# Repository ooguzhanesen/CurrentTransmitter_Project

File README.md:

# CURRENT TRANSMITTER KARTI
## KART ÖZELLİKLERİ
- 3 ADET  4-20 mA analog çıkış
- STM32f103C8 mikrodenetleyici 
- RS485 Portu
- 7-28 volt güç girişi
- Aşırı votaj koruması
- Ters bağlantı koruması
- Akım limitleyici

## PCB TASARIM
CURRENT TRANSITTER kartı 4 katlı olacak şekilde KiCad üzerinden tasarlandı. 3 DAC'ın ve Mikrodenetleyicinin GND'leri birbirinden izole şekilde çizildi. PCB, DT-0505 kutusuna uygun olacak şekilde tasarlandı.

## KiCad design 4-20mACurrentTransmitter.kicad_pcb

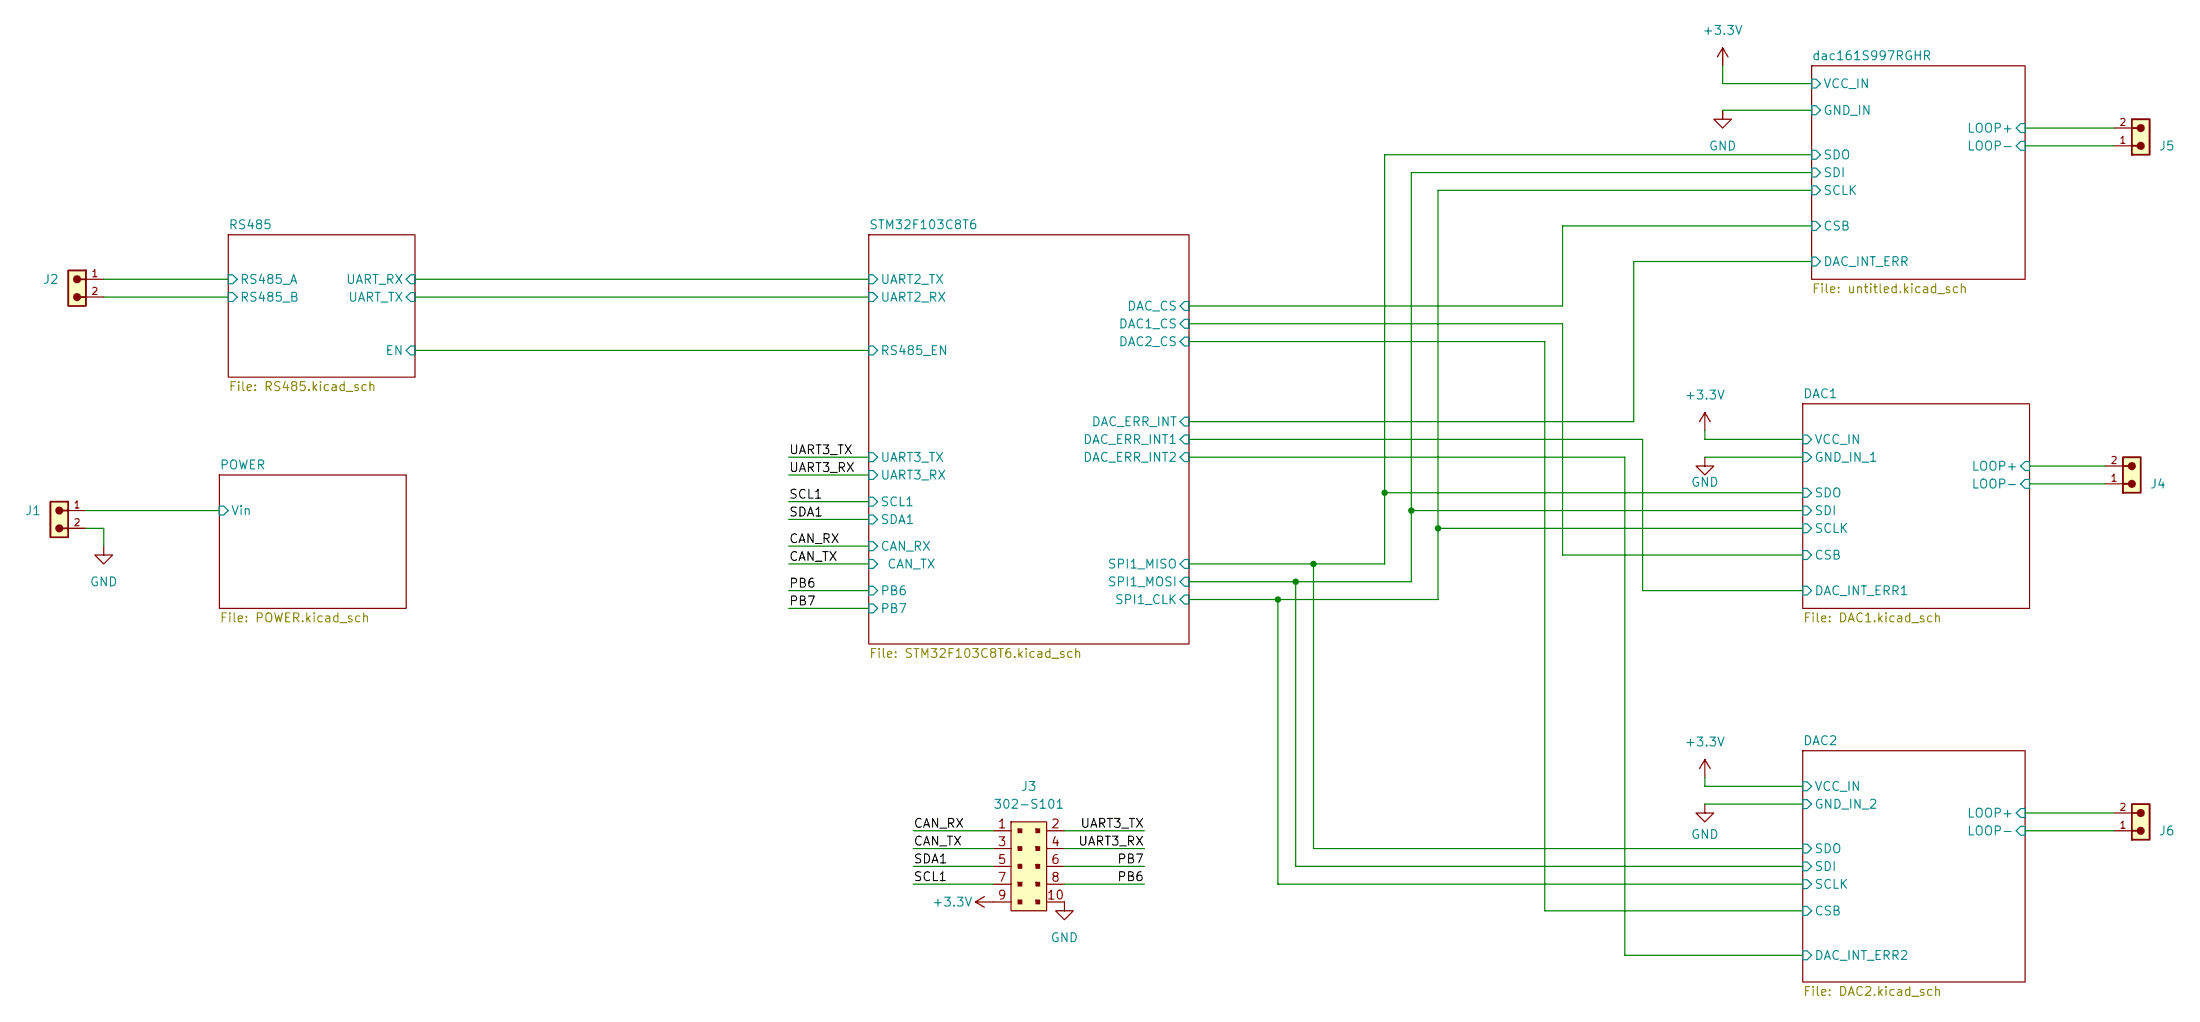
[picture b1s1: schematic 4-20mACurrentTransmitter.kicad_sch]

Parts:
J1, J2, J4, J5, J6: 691322310002; PART-NUMBER 691322310002; DigiKey 732-2088-ND
J3: 302-S101; PinHeader_2x5_P2.54mm_Drill1.2mm; MPN 302-S101; DigiKey ED1543-ND

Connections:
+3.3V: J3.9; also elsewhere on the board
/CAN_RX: J3.1; also elsewhere on the board
/CAN_TX: J3.3; also elsewhere on the board
/DAC1/LOOP+: J4.2; also elsewhere on the board
/DAC1/LOOP-: J4.1; also elsewhere on the board
/DAC2/LOOP+: J6.2; also elsewhere on the board
/DAC2/LOOP-: J6.1; also elsewhere on the board
/PB6: J3.8; also elsewhere on the board
/PB7: J3.6; also elsewhere on the board
/POWER/Vin: J1.1; also elsewhere on the board
/RS485/RS485_A: J2.1; also elsewhere on the board
/RS485/RS485_B: J2.2; also elsewhere on the board
/SCL1: J3.7; also elsewhere on the board
/SDA1: J3.5; also elsewhere on the board
/UART3_RX: J3.4; also elsewhere on the board
/UART3_TX: J3.2; also elsewhere on the board
/dac161S997RGHR/LOOP+: J5.2; also elsewhere on the board
/dac161S997RGHR/LOOP-: J5.1; also elsewhere on the board

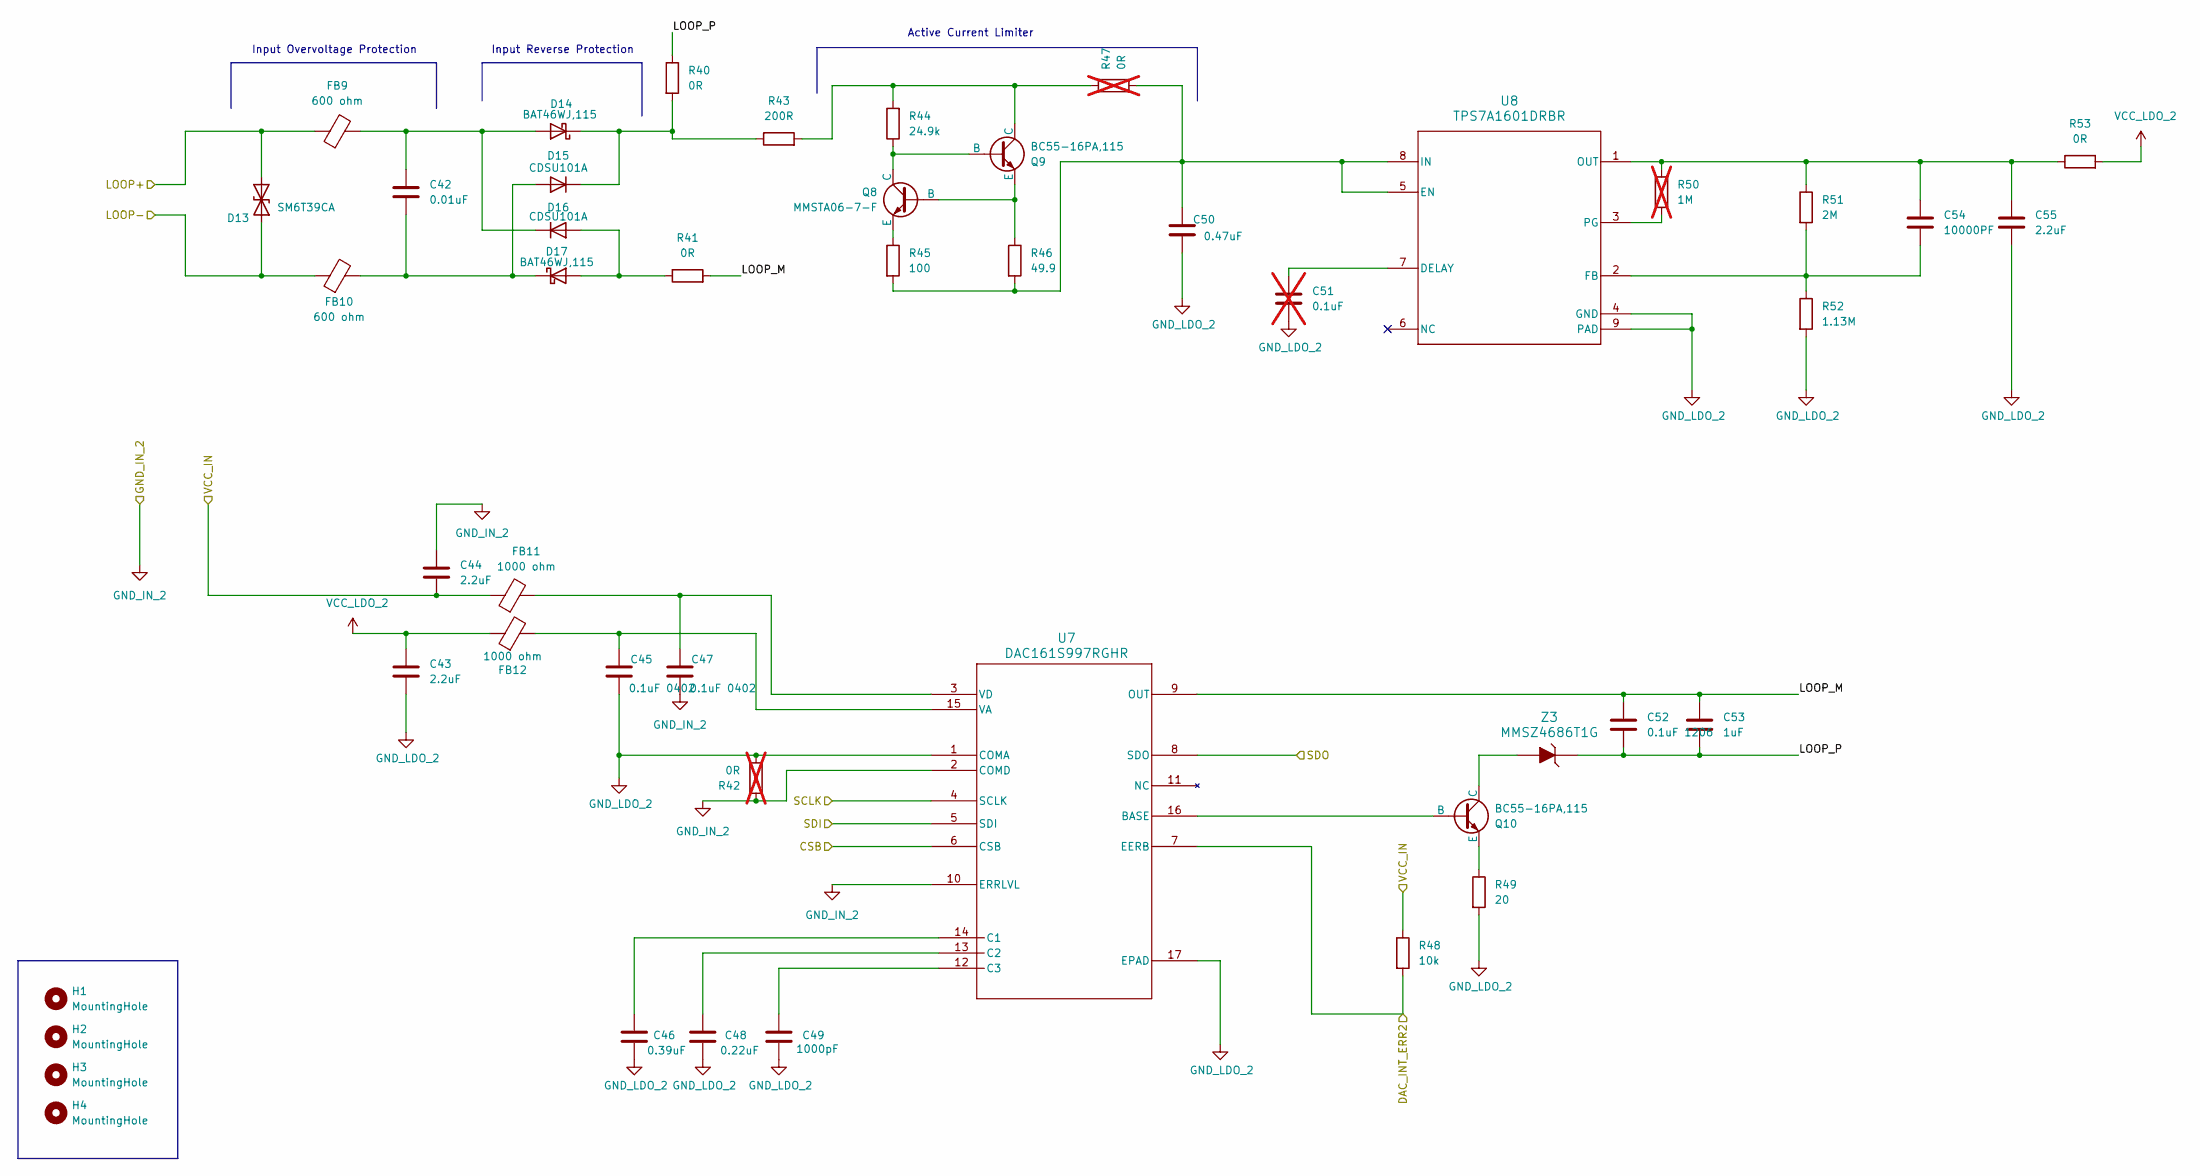
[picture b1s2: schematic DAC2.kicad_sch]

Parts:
C42: 0.01uF; C_0603_1608Metric; DIGIKEY 445-1304-2-ND
C43, C44, C55: 2.2uF; C_0402_1005Metric; DIGIKEY 445-9085-2-ND
C45, C47: 0.1uF 0402; C_0402_1005Metric; DIGIKEY 445-1266-2-ND
C46: 0.39uF; C_0402_1005Metric; DIGIKEY 490-8253-2-ND
C48: 0.22uF; C_0402_1005Metric; DIGIKEY 490-5407-2-ND
C49: 1000pF; C_0402_1005Metric; DIGIKEY 490-6285-2-ND
C50: 0.47uF; C_0805_2012Metric; DIGIKEY 490-3326-2-ND
C51: 0.1uF; C_1206_3216Metric; DIGIKEY 478-KGM31DR72A104JUTR-ND; not fitted
C52: 0.1uF 1206; C_1206_3216Metric; DIGIKEY 478-KGM31DR72A104JUTR-ND
C53: 1uF; C_1206_3216Metric; DIGIKEY 490-3909-2-ND
C54: 10000PF; C_0402_1005Metric; DIGIKEY 490-6296-2-ND
D13: SM6T39CA; D_SMB; DIGIKEY 497-6498-2-ND
D14, D17: BAT46WJ,115; D_SOD-323F; DIGIKEY 1727-4817-2-ND
D15, D16: CDSU101A; LED_CDSU101A; DIGIKEY 641-1002-2-ND
FB9, FB10: 600 ohm; R_1206_3216Metric; DIGIKEY 240-2405-2-ND
FB11, FB12: 1000 ohm; R_0402_1005Metric; DIGIKEY 490-3999-2-ND
H1, H2, H3, H4: MountingHole; MountingHole_3.2mm_M3_DIN965_Pad
Q8: MMSTA06-7-F; SOT-323; DIGIKEY MMSTA06-FDITR-ND
Q9, Q10: BC55-16PA,115; 3-HUSON(2X2); DIGIKEY 1727-2344-2-ND
R40, R41, R53: 0R; R_0603_1608Metric; DIGIKEY 541-0.0GTR-ND
R42, R47: 0R; R_0603_1608Metric; DIGIKEY 541-0.0GTR-ND; not fitted
R43: 200R; R_1206_3216Metric; DIGIKEY 541-200FTR-ND
R44: 24.9k; R_0603_1608Metric; DIGIKEY 541-4028-2-ND
R45: 100; R_0603_1608Metric; DIGIKEY 541-100STR-ND
R46: 49.9; R_1206_3216Metric; DIGIKEY 541-4185-2-ND
R48: 10k; R_0402_1005Metric; DIGIKEY 311-10KJRTR-ND
R49: 20; R_0603_1608Metric; DIGIKEY 541-20.0HTR-ND
R50: 1M; R_0402_1005Metric; DIGIKEY 541-4119-2-ND; not fitted
R51: 2M; R_0402_1005Metric; DIGIKEY 541-4066-2-ND
R52: 1.13M; R_0402_1005Metric; DIGIKEY 541-1.13MLTR-ND
U7: DAC161S997RGHR; RGH16_TEX; DIGIKEY 296-40022-2-ND
U8: TPS7A1601DRBR; DRB0008B; DIGIKEY 96-40969-2-ND
Z3: MMSZ4686T1G; SOD-123; DIGIKEY MMSZ4686T1GOSTR-ND

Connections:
+3.3V: C44.2, FB11.1, R48.1; also elsewhere on the board
/DAC1/SCLK: U7.4 (SCLK); also elsewhere on the board
/DAC1/SDI: U7.5 (SDI); also elsewhere on the board
/DAC1/SDO: U7.8 (SDO); also elsewhere on the board
/DAC2/CSB: U7.6 (CSB); also elsewhere on the board
/DAC2/DAC_INT_ERR2: R48.2, U7.7 (EERB); also elsewhere on the board
/DAC2/LOOP+: D13.1 (A1), FB9.1; also elsewhere on the board
/DAC2/LOOP-: D13.2 (A2), FB10.1; also elsewhere on the board
/DAC2/LOOP_M: C52.1, C53.1, R41.2, U7.9 (OUT)
/DAC2/LOOP_P: C52.2, C53.2, R40.1, Z3.K
GND_LDO_2: C43.2, C45.2, C46.2, C48.2, C49.2, C50.2, C51.2, C55.2, R42.2, R49.2, R52.2, U7.1 (COMA), U7.17 (EPAD), U8.4 (GND), U8.9 (PAD)
unnamed: C42.1, D14.2 (A), D16.1 (K), FB9.2
unnamed: D14.1 (K), D15.1 (K), R40.2, R43.1
unnamed: C42.2, D15.2 (A), D17.1 (K), FB10.2
unnamed: D16.2 (A), D17.2 (A), R41.1
unnamed: Q8.2 (B), Q9.3 (E), R46.1
unnamed: Q8.1 (C), Q9.2 (B), R44.1
unnamed: Q8.3 (E), R45.1
unnamed: Q9.1 (C), R43.2, R44.2, R47.1
unnamed: Q10.2 (B), U7.16 (BASE)
unnamed: Q10.1 (C), Z3.A
unnamed: Q10.3 (E), R49.1
unnamed: C46.1, U7.14 (C1)
unnamed: C48.1, U7.13 (C2)
unnamed: C49.1, U7.12 (C3)
unnamed: C45.1, FB12.2, U7.15 (VA)
unnamed: C47.1, FB11.2, U7.3 (VD)
unnamed: C51.1, U8.7 (DELAY)
unnamed: C50.1, R45.2, R46.2, R47.2, U8.5 (EN), U8.8 (IN)
unnamed: C54.2, R51.2, R52.1, U8.2 (FB)
unnamed: C54.1, C55.1, R50.1, R51.1, R53.1, U8.1 (OUT)
unnamed: R50.2, U8.3 (PG)
VCC_LDO_2: C43.1, FB12.1, R53.2

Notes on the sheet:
Input Overvoltage Protection
Input Reverse Protection
Active Current Limiter

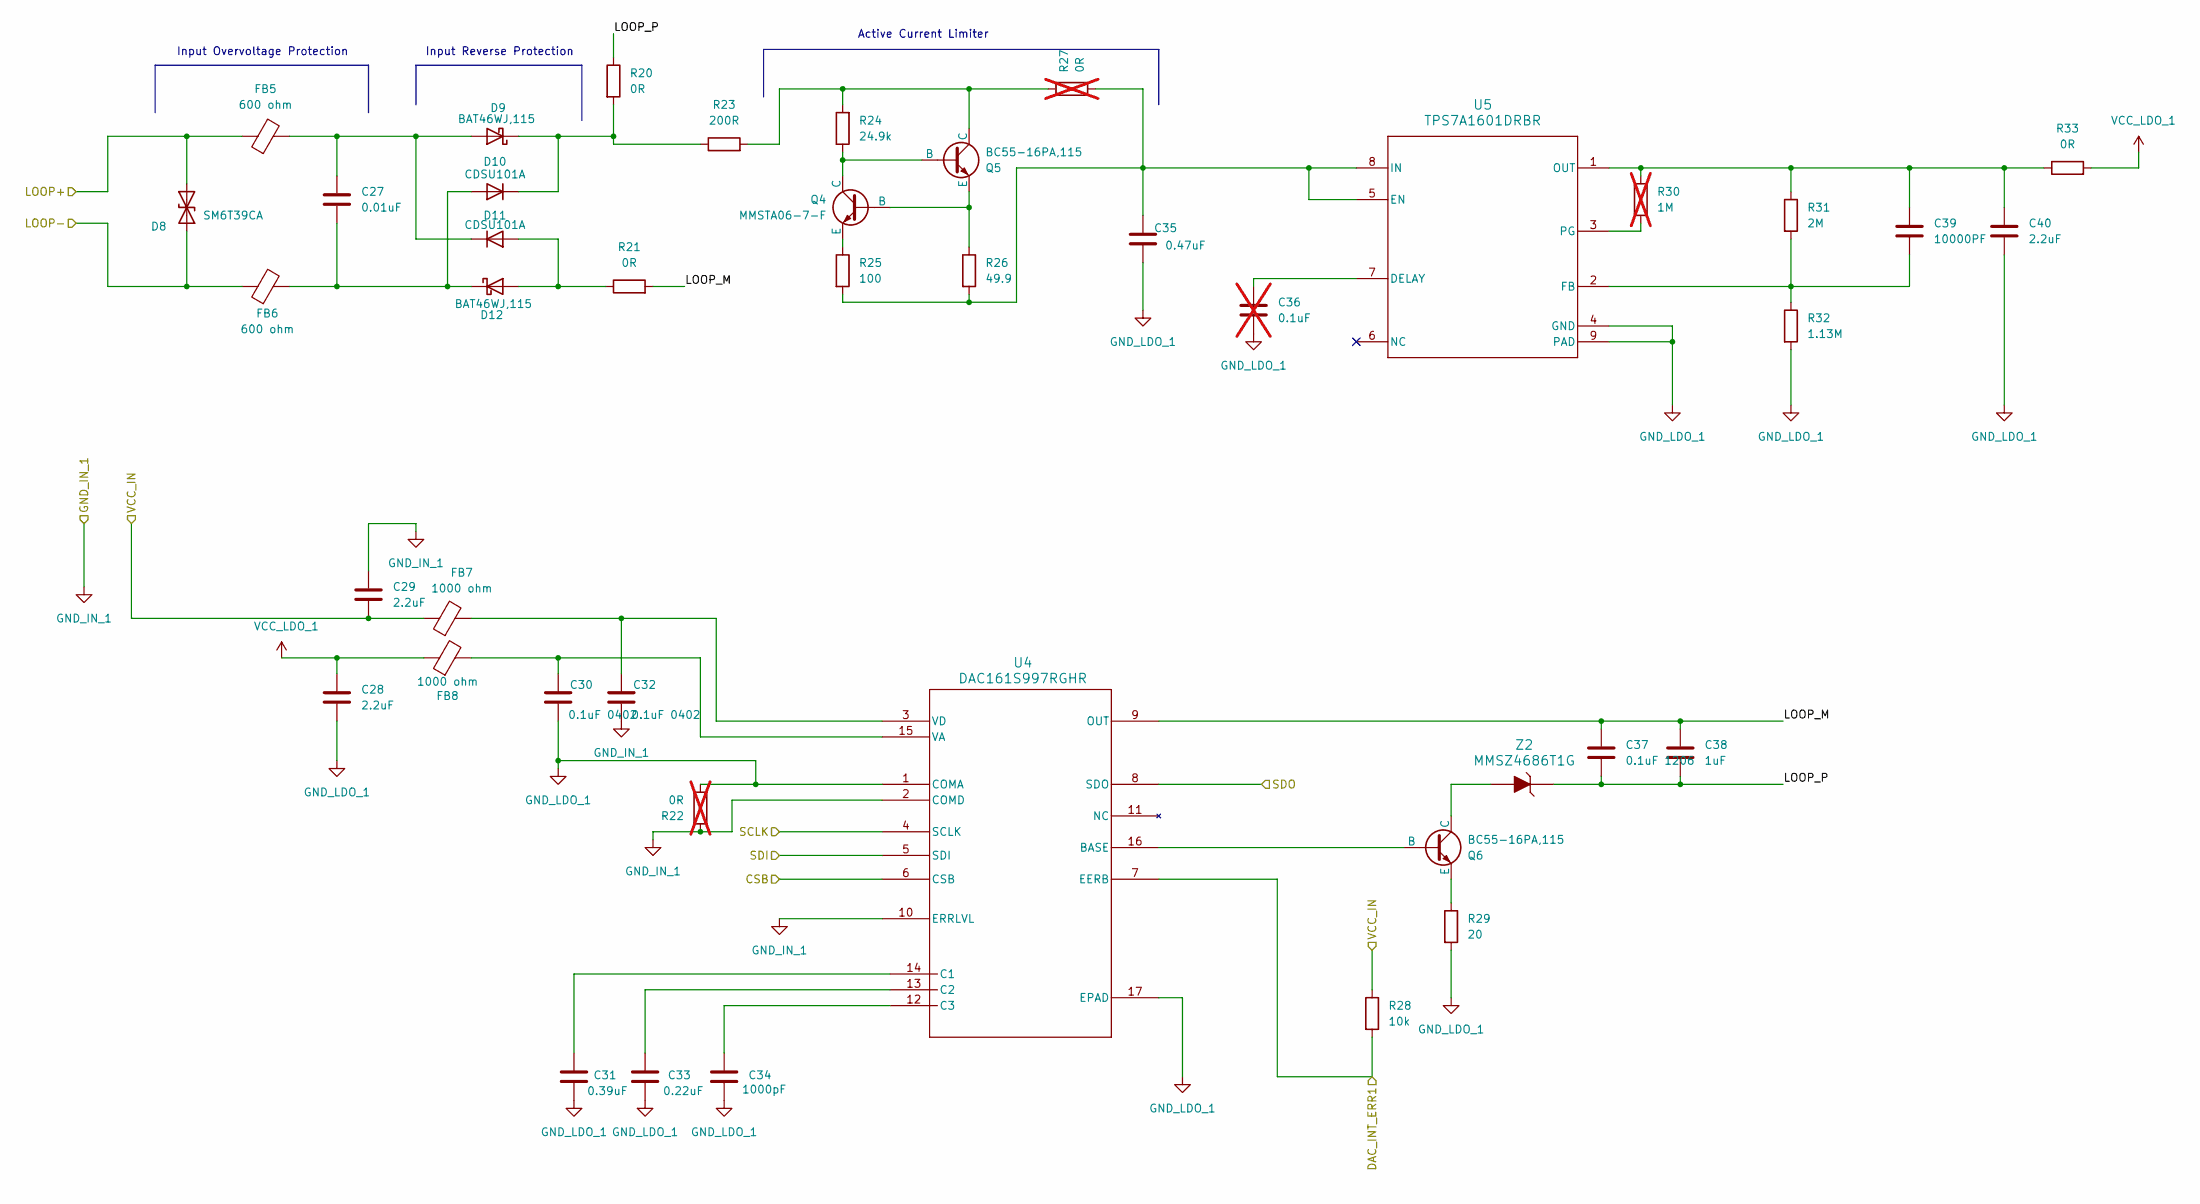
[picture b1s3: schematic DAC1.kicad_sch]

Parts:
C27: 0.01uF; C_0603_1608Metric; DIGIKEY 445-1304-2-ND
C28, C29, C40: 2.2uF; C_0402_1005Metric; DIGIKEY 445-9085-2-ND
C30, C32: 0.1uF 0402; C_0402_1005Metric; DIGIKEY 445-1266-2-ND
C31: 0.39uF; C_0402_1005Metric; DIGIKEY 490-8253-2-ND
C33: 0.22uF; C_0402_1005Metric; DIGIKEY 490-5407-2-ND
C34: 1000pF; C_0402_1005Metric; DIGIKEY 490-6285-2-ND
C35: 0.47uF; C_0805_2012Metric; DIGIKEY 490-3326-2-ND
C36: 0.1uF; C_1206_3216Metric; DIGIKEY 478-KGM31DR72A104JUTR-ND; not fitted
C37: 0.1uF 1206; C_1206_3216Metric; DIGIKEY 478-KGM31DR72A104JUTR-ND
C38: 1uF; C_1206_3216Metric; DIGIKEY 490-3909-2-ND
C39: 10000PF; C_0402_1005Metric; DIGIKEY 490-6296-2-ND
D8: SM6T39CA; D_SMB; DIGIKEY 497-6498-2-ND
D9, D12: BAT46WJ,115; D_SOD-323F; DIGIKEY 1727-4817-2-ND
D10, D11: CDSU101A; LED_CDSU101A; DIGIKEY 641-1002-2-ND
FB5, FB6: 600 ohm; R_1206_3216Metric; DIGIKEY 240-2405-2-ND
FB7, FB8: 1000 ohm; R_0402_1005Metric; DIGIKEY 490-3999-2-ND
Q4: MMSTA06-7-F; SOT-323; DIGIKEY MMSTA06-FDITR-ND
Q5, Q6: BC55-16PA,115; 3-HUSON(2X2); DIGIKEY 1727-2344-2-ND
R20, R21, R33: 0R; R_0603_1608Metric; DIGIKEY 541-0.0GTR-ND
R22, R27: 0R; R_0603_1608Metric; DIGIKEY 541-0.0GTR-ND; not fitted
R23: 200R; R_1206_3216Metric; DIGIKEY 541-200FTR-ND
R24: 24.9k; R_0603_1608Metric; DIGIKEY 541-4028-2-ND
R25: 100; R_0603_1608Metric; DIGIKEY 541-100STR-ND
R26: 49.9; R_1206_3216Metric; DIGIKEY 541-4185-2-ND
R28: 10k; R_0402_1005Metric; DIGIKEY 311-10KJRTR-ND
R29: 20; R_0603_1608Metric; DIGIKEY 541-20.0HTR-ND
R30: 1M; R_0402_1005Metric; DIGIKEY 541-4119-2-ND; not fitted
R31: 2M; R_0402_1005Metric; DIGIKEY 541-4066-2-ND
R32: 1.13M; R_0402_1005Metric; DIGIKEY 541-1.13MLTR-ND
U4: DAC161S997RGHR; RGH16_TEX; DIGIKEY 296-40022-2-ND
U5: TPS7A1601DRBR; DRB0008B; DIGIKEY 96-40969-2-ND
Z2: MMSZ4686T1G; SOD-123; DIGIKEY MMSZ4686T1GOSTR-ND

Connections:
+3.3V: C29.2, FB7.1, R28.1; also elsewhere on the board
/DAC1/CSB: U4.6 (CSB); also elsewhere on the board
/DAC1/DAC_INT_ERR1: R28.2, U4.7 (EERB); also elsewhere on the board
/DAC1/LOOP+: D8.1 (A1), FB5.1; also elsewhere on the board
/DAC1/LOOP-: D8.2 (A2), FB6.1; also elsewhere on the board
/DAC1/LOOP_M: C37.1, C38.1, R21.2, U4.9 (OUT)
/DAC1/LOOP_P: C37.2, C38.2, R20.1, Z2.K
/DAC1/SCLK: U4.4 (SCLK); also elsewhere on the board
/DAC1/SDI: U4.5 (SDI); also elsewhere on the board
/DAC1/SDO: U4.8 (SDO); also elsewhere on the board
GND_LDO_1: C28.2, C30.2, C31.2, C33.2, C34.2, C35.2, C36.2, C40.2, R22.2, R29.2, R32.2, U4.1 (COMA), U4.17 (EPAD), U5.4 (GND), U5.9 (PAD)
unnamed: C27.2, D10.2 (A), D12.1 (K), FB6.2
unnamed: D9.1 (K), D10.1 (K), R20.2, R23.1
unnamed: D11.2 (A), D12.2 (A), R21.1
unnamed: C27.1, D9.2 (A), D11.1 (K), FB5.2
unnamed: Q4.2 (B), Q5.3 (E), R26.1
unnamed: Q4.1 (C), Q5.2 (B), R24.1
unnamed: Q4.3 (E), R25.1
unnamed: Q5.1 (C), R23.2, R24.2, R27.1
unnamed: Q6.2 (B), U4.16 (BASE)
unnamed: Q6.1 (C), Z2.A
unnamed: Q6.3 (E), R29.1
unnamed: C31.1, U4.14 (C1)
unnamed: C33.1, U4.13 (C2)
unnamed: C34.1, U4.12 (C3)
unnamed: C30.1, FB8.2, U4.15 (VA)
unnamed: C32.1, FB7.2, U4.3 (VD)
unnamed: C36.1, U5.7 (DELAY)
unnamed: C35.1, R25.2, R26.2, R27.2, U5.5 (EN), U5.8 (IN)
unnamed: C39.2, R31.2, R32.1, U5.2 (FB)
unnamed: C39.1, C40.1, R30.1, R31.1, R33.1, U5.1 (OUT)
unnamed: R30.2, U5.3 (PG)
VCC_LDO_1: C28.1, FB8.1, R33.2

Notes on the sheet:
Input Overvoltage Protection
Input Reverse Protection
Active Current Limiter

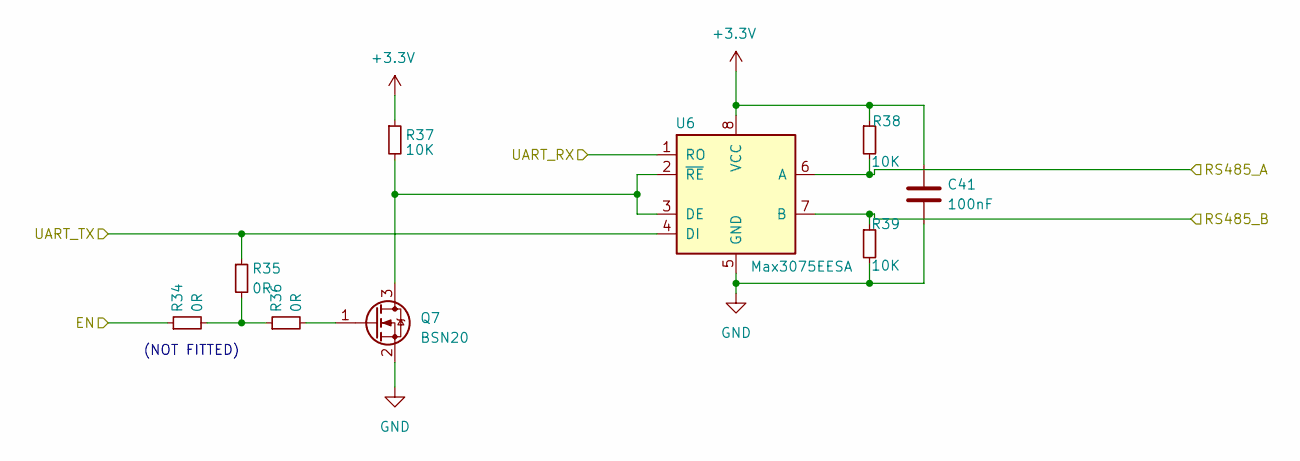
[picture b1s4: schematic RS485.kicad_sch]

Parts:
C41: 100nF; C_0402_1005Metric; DIGIKEY 3372-0402B104K500HITR-ND
Q7: BSN20; SOT-23; DIGIKEY BSN20-7DITR-ND
R34, R35, R36: 0R; R_0603_1608Metric; DIGIKEY 541-0.0GTR-ND
R37, R38, R39: 10K; R_0603_1608Metric; DIGIKEY 311-10.0KHRTR-ND
U6: Max3075EESA; SOIC-8_3.9x4.9mm_P1.27mm; DIGIKEY MAX3075EESA+-ND

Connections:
+3.3V: C41.1, R37.1, R38.1, U6.8 (VCC); also elsewhere on the board
/RS485/EN: R34.1; also elsewhere on the board
/RS485/RS485_A: R38.2, U6.6 (A); also elsewhere on the board
/RS485/RS485_B: R39.1, U6.7 (B); also elsewhere on the board
/RS485/UART_RX: U6.1 (RO); also elsewhere on the board
/RS485/UART_TX: R35.1, U6.4 (DI); also elsewhere on the board
unnamed: Q7.3 (D), R37.2, U6.2 (~RE), U6.3 (DE)
unnamed: Q7.1 (G), R36.2
unnamed: R34.2, R35.2, R36.1

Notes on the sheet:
(NOT FITTED)

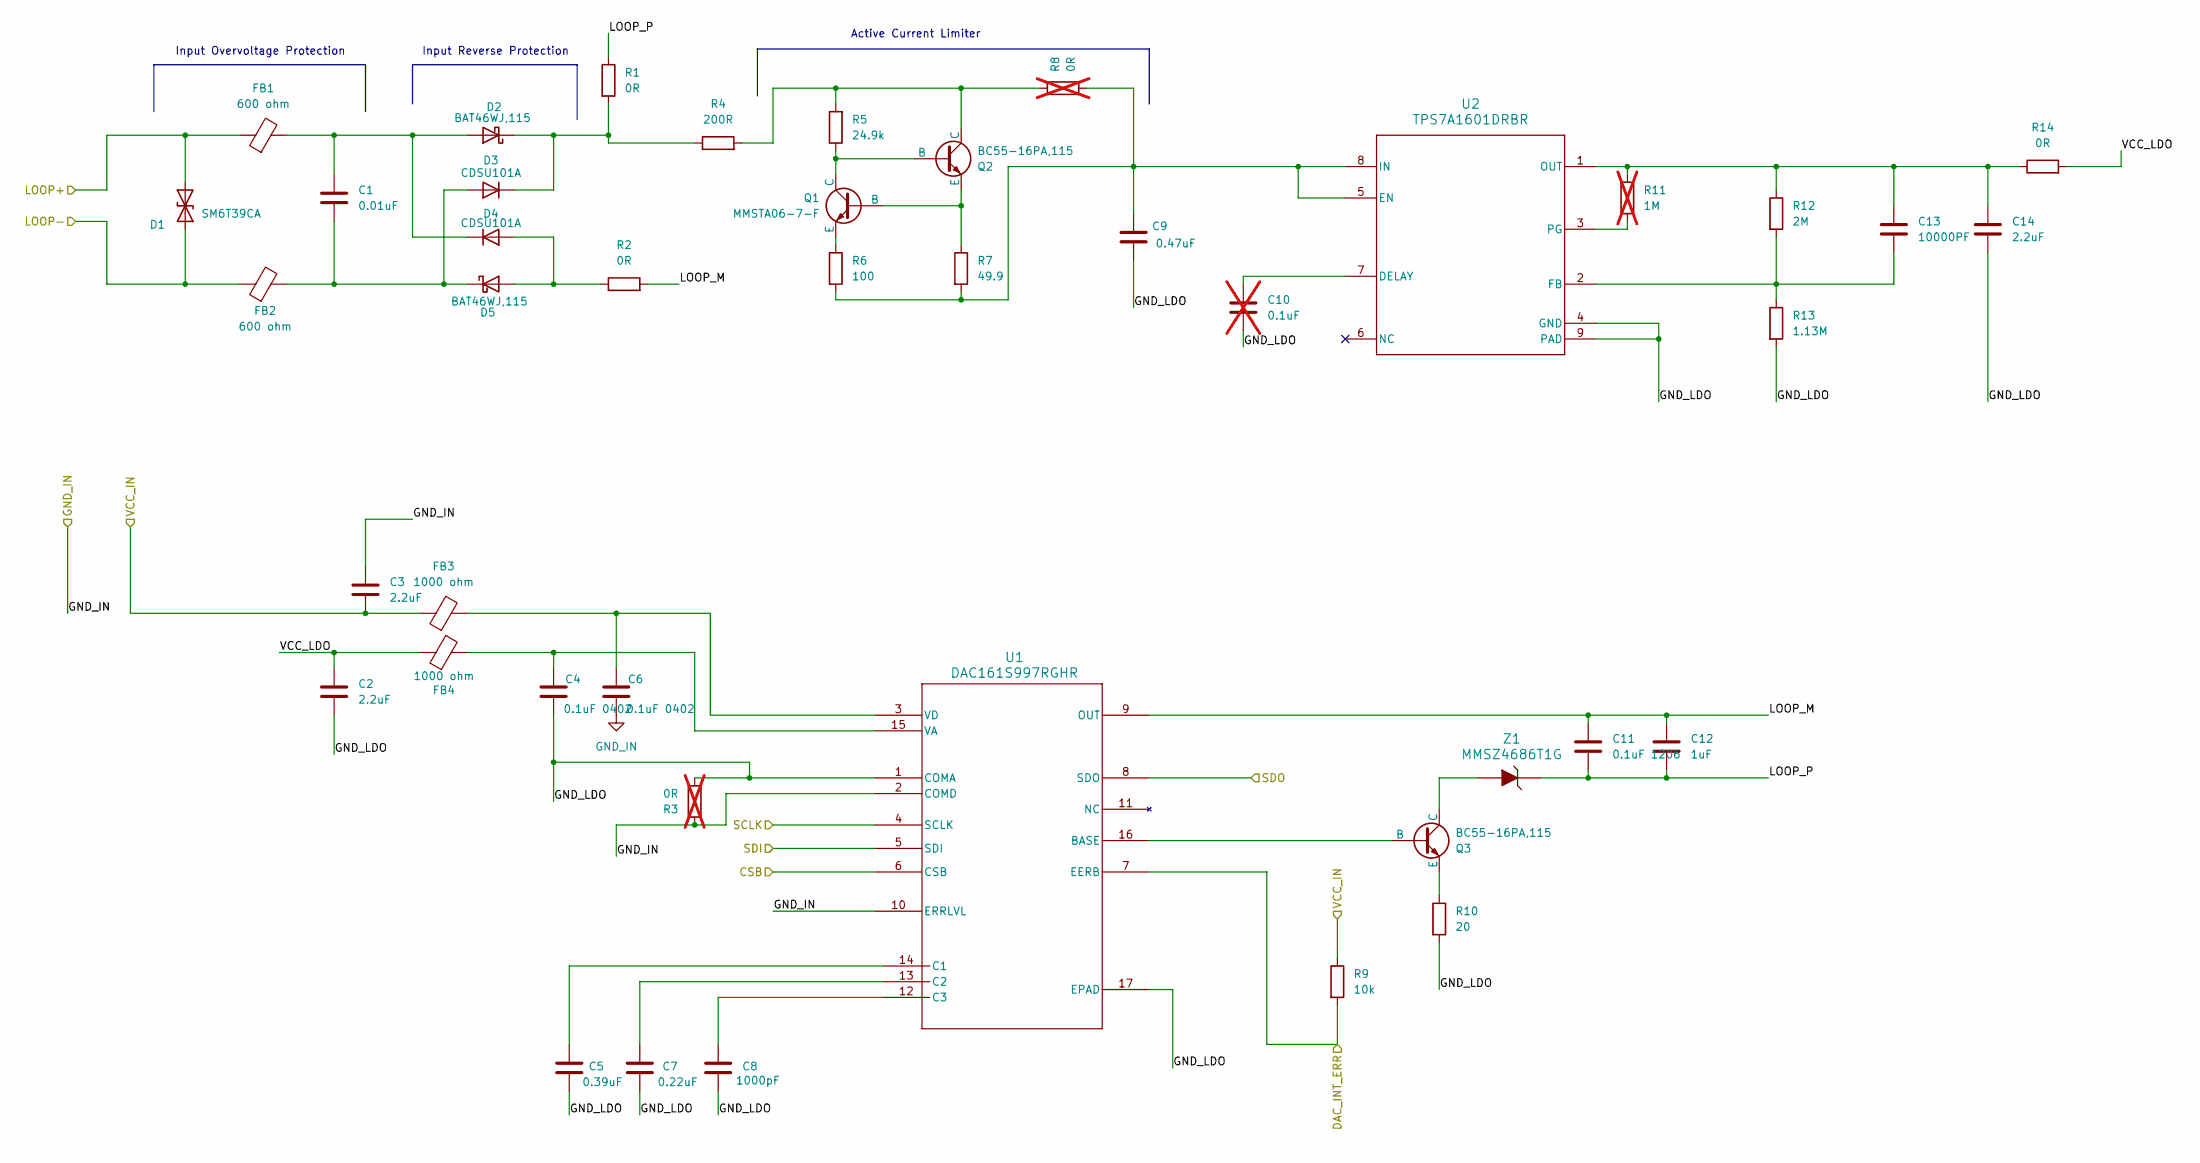
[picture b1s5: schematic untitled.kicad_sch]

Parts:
C1: 0.01uF; C_0603_1608Metric; DIGIKEY 445-1304-2-ND
C2, C3, C14: 2.2uF; C_0402_1005Metric; DIGIKEY 445-9085-2-ND
C4, C6: 0.1uF 0402; C_0402_1005Metric; DIGIKEY 445-1266-2-ND
C5: 0.39uF; C_0402_1005Metric; DIGIKEY 490-8253-2-ND
C7: 0.22uF; C_0402_1005Metric; DIGIKEY 490-5407-2-ND
C8: 1000pF; C_0402_1005Metric; DIGIKEY 490-6285-2-ND
C9: 0.47uF; C_0805_2012Metric; DIGIKEY 490-3326-2-ND
C10: 0.1uF; C_1206_3216Metric; DIGIKEY 478-KGM31DR72A104JUTR-ND; not fitted
C11: 0.1uF 1206; C_1206_3216Metric; DIGIKEY 478-KGM31DR72A104JUTR-ND
C12: 1uF; C_1206_3216Metric; DIGIKEY 490-3909-2-ND
C13: 10000PF; C_0402_1005Metric; DIGIKEY 490-6296-2-ND
D1: SM6T39CA; D_SMB; DIGIKEY 497-6498-2-ND
D2, D5: BAT46WJ,115; D_SOD-323F; DIGIKEY 1727-4817-2-ND
D3, D4: CDSU101A; LED_CDSU101A; DIGIKEY 641-1002-2-ND
FB1, FB2: 600 ohm; R_1206_3216Metric; DIGIKEY 240-2405-2-ND
FB3, FB4: 1000 ohm; R_0402_1005Metric; DIGIKEY 490-3999-2-ND
Q1: MMSTA06-7-F; SOT-323; DIGIKEY MMSTA06-FDITR-ND
Q2, Q3: BC55-16PA,115; 3-HUSON(2X2); DIGIKEY 1727-2344-2-ND
R1, R2, R14: 0R; R_0603_1608Metric; DIGIKEY 541-0.0GTR-ND
R3, R8: 0R; R_0603_1608Metric; DIGIKEY 541-0.0GTR-ND; not fitted
R4: 200R; R_1206_3216Metric; DIGIKEY 541-200FTR-ND
R5: 24.9k; R_0603_1608Metric; DIGIKEY 541-4028-2-ND
R6: 100; R_0603_1608Metric; DIGIKEY 541-100STR-ND
R7: 49.9; R_1206_3216Metric; DIGIKEY 541-4185-2-ND
R9: 10k; R_0402_1005Metric; DIGIKEY 311-10KJRTR-ND
R10: 20; R_0603_1608Metric; DIGIKEY 541-20.0HTR-ND
R11: 1M; R_0402_1005Metric; DIGIKEY 541-4119-2-ND; not fitted
R12: 2M; R_0402_1005Metric; DIGIKEY 541-4066-2-ND
R13: 1.13M; R_0402_1005Metric; DIGIKEY 541-1.13MLTR-ND
U1: DAC161S997RGHR; RGH16_TEX; DIGIKEY 296-40022-2-ND
U2: TPS7A1601DRBR; DRB0008B; DIGIKEY 96-40969-2-ND
Z1: MMSZ4686T1G; SOD-123; DIGIKEY MMSZ4686T1GOSTR-ND

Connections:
+3.3V: C3.2, FB3.1, R9.1; also elsewhere on the board
/DAC1/SCLK: U1.4 (SCLK); also elsewhere on the board
/DAC1/SDI: U1.5 (SDI); also elsewhere on the board
/DAC1/SDO: U1.8 (SDO); also elsewhere on the board
/STM32F103C8T6/DAC_CS: U1.6 (CSB); also elsewhere on the board
/STM32F103C8T6/DAC_ERR_INT: R9.2, U1.7 (EERB); also elsewhere on the board
/dac161S997RGHR/GND_LDO: C2.2, C4.2, C5.2, C7.2, C8.2, C9.2, C10.2, C14.2, R3.2, R10.2, R13.2, U1.1 (COMA), U1.17 (EPAD), U2.4 (GND), U2.9 (PAD)
/dac161S997RGHR/LOOP+: D1.1 (A1), FB1.1; also elsewhere on the board
/dac161S997RGHR/LOOP-: D1.2 (A2), FB2.1; also elsewhere on the board
/dac161S997RGHR/LOOP_M: C11.1, C12.1, R2.2, U1.9 (OUT)
/dac161S997RGHR/LOOP_P: C11.2, C12.2, R1.1, Z1.K
/dac161S997RGHR/VCC_LDO: C2.1, FB4.1, R14.2
unnamed: C1.1, D2.2 (A), D4.1 (K), FB1.2
unnamed: D2.1 (K), D3.1 (K), R1.2, R4.1
unnamed: C1.2, D3.2 (A), D5.1 (K), FB2.2
unnamed: D4.2 (A), D5.2 (A), R2.1
unnamed: Q1.2 (B), Q2.3 (E), R7.1
unnamed: Q1.1 (C), Q2.2 (B), R5.1
unnamed: Q1.3 (E), R6.1
unnamed: Q2.1 (C), R4.2, R5.2, R8.1
unnamed: Q3.2 (B), U1.16 (BASE)
unnamed: Q3.1 (C), Z1.A
unnamed: Q3.3 (E), R10.1
unnamed: C5.1, U1.14 (C1)
unnamed: C7.1, U1.13 (C2)
unnamed: C8.1, U1.12 (C3)
unnamed: C4.1, FB4.2, U1.15 (VA)
unnamed: C6.1, FB3.2, U1.3 (VD)
unnamed: C10.1, U2.7 (DELAY)
unnamed: C9.1, R6.2, R7.2, R8.2, U2.5 (EN), U2.8 (IN)
unnamed: C13.2, R12.2, R13.1, U2.2 (FB)
unnamed: C13.1, C14.1, R11.1, R12.1, R14.1, U2.1 (OUT)
unnamed: R11.2, U2.3 (PG)

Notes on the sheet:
Active Current Limiter
Input Overvoltage Protection
Input Reverse Protection

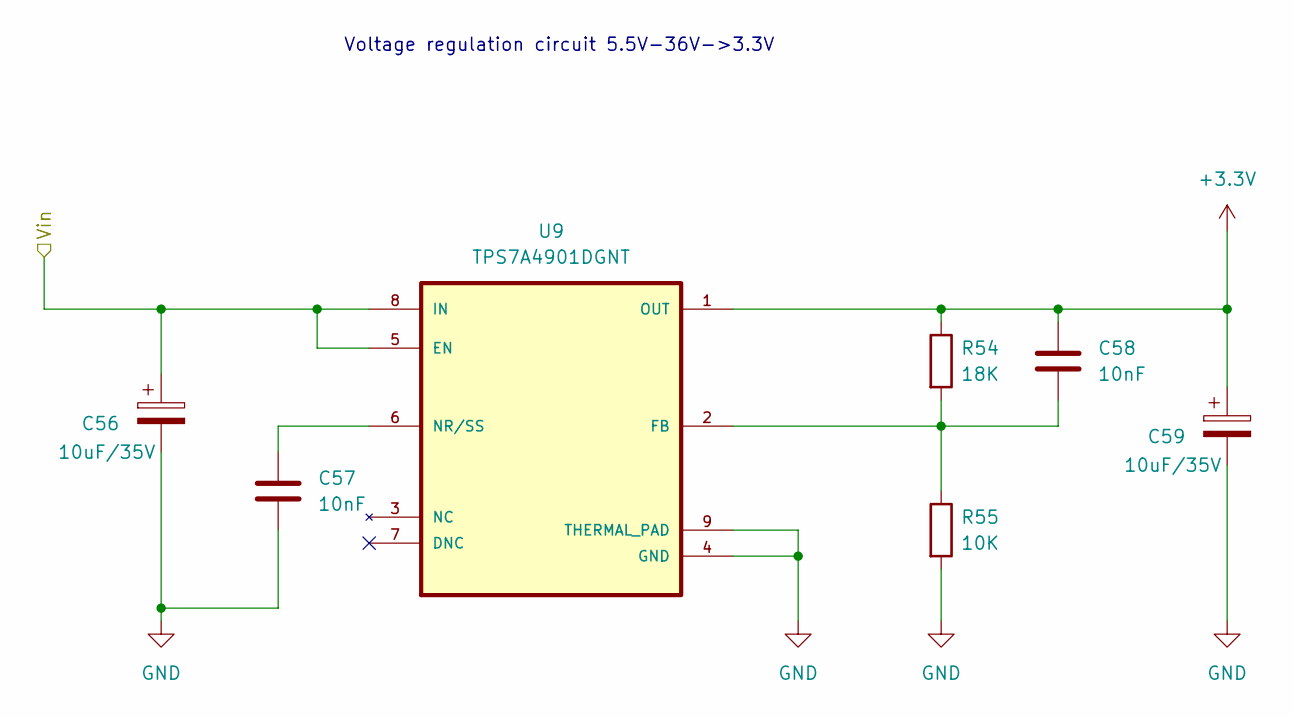
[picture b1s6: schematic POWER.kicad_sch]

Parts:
C56, C59: 10uF/35V; CP_Elec_5x5.4; DIGIKEY 732-8295-2-ND
C57, C58: 10nF; C_0603_1608Metric; DIGIKEY 399-C0603C103K4RECTUTR-ND
R54: 18K; R_0603_1608Metric; DIGIKEY 11-18KGRTR-ND
R55: 10K; R_0603_1608Metric; DIGIKEY 311-10.0KHRTR-ND
U9: TPS7A4901DGNT; SOP65P490X110-9N; DIGIKEY TPS7A4901DGNT

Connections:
+3.3V: C58.1, C59.1, R54.1, U9.1 (OUT); also elsewhere on the board
/POWER/Vin: C56.1, U9.5 (EN), U9.8 (IN); also elsewhere on the board
unnamed: C58.2, R54.2, R55.1, U9.2 (FB)
unnamed: C57.1, U9.6 (NR/SS)

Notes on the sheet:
Voltage regulation circuit 5.5V-36V->3.3V

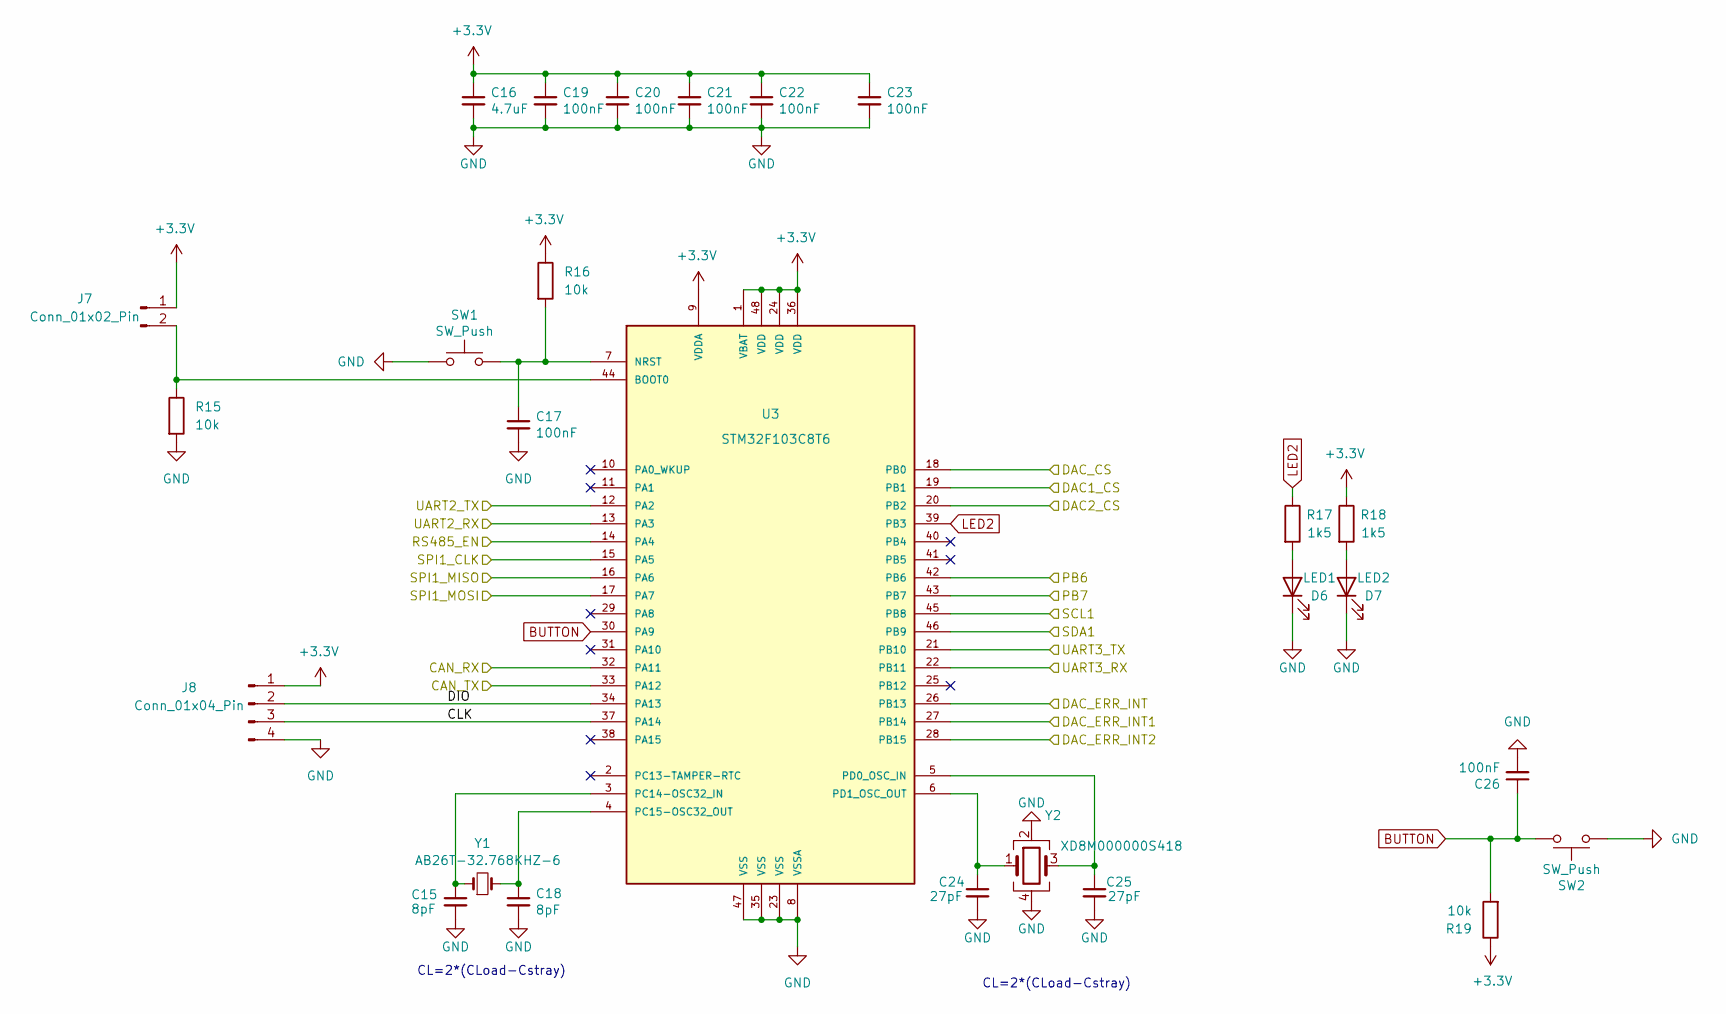
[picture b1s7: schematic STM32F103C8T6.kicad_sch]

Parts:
C15, C18: 8pF; C_0402_1005Metric; DIGIKEY 490-8230-2-ND
C16: 4.7uF; C_0603_1608Metric; DIGIKEY 3372-0603W475K100XDTR-ND
C17, C19, C20, C21, C22, C23, C26: 100nF; C_0402_1005Metric; DIGIKEY 3372-0402B104K500HITR-ND
C24, C25: 27pF; C_0402_1005Metric; DIGIKEY 2571-GMC04CG270G50NTTR-ND
D6: LED1; LED_0603_1608Metric; DIGIKEY 5859-YY0603YG-NN3S0-T2AR4TR-ND
D7: LED2; LED_0603_1608Metric; DIGIKEY 5859-YY0603RE-NN3S0-T2AR4TR-ND
J7: Conn_01x02_Pin; PinHeader_1x02_P2.54mm_Vertical; DIGIKEY 952-2262-ND
J8: Conn_01x04_Pin; PinHeader_1x04_P2.54mm_Vertical; DIGIKEY 732-5317-ND
R15, R16, R19: 10k; R_0402_1005Metric; DIGIKEY 311-10KJRTR-ND
R17, R18: 1k5; R_0603_1608Metric; DIGIKEY 311-1.5KGRTR-ND
SW1, SW2: SW_Push; pushbutton; DIGIKEY 1825910-6
U3: STM32F103C8T6; LQFP48_STM; DIGIKEY 497-6063-ND
Y1: AB26T-32.768KHZ-6; XTAL_AB26T-32.768KHZ-6; DIGIKEY 535-AB26T-32.768KHZ-6TR-ND
Y2: XD8M000000S418; Crystal_SMD_EuroQuartz_MJ-4Pin_5.0x3.2mm; DIGIKEY XD8M000000S418

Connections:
+3.3V: C16.1, C19.1, C20.1, C21.1, C22.1, C23.1, J7.1, J8.1, R16.1, R18.1, R19.1, U3.1 (VBAT), U3.9 (VDDA), U3.24 (VDD), U3.36 (VDD), U3.48 (VDD); also elsewhere on the board
/CAN_RX: U3.32 (PA11); also elsewhere on the board
/CAN_TX: U3.33 (PA12); also elsewhere on the board
/DAC1/CSB: U3.19 (PB1); also elsewhere on the board
/DAC1/DAC_INT_ERR1: U3.27 (PB14); also elsewhere on the board
/DAC1/SCLK: U3.15 (PA5); also elsewhere on the board
/DAC1/SDI: U3.17 (PA7); also elsewhere on the board
/DAC1/SDO: U3.16 (PA6); also elsewhere on the board
/DAC2/CSB: U3.20 (PB2); also elsewhere on the board
/DAC2/DAC_INT_ERR2: U3.28 (PB15); also elsewhere on the board
/PB6: U3.42 (PB6); also elsewhere on the board
/PB7: U3.43 (PB7); also elsewhere on the board
/RS485/EN: U3.14 (PA4); also elsewhere on the board
/RS485/UART_RX: U3.12 (PA2); also elsewhere on the board
/RS485/UART_TX: U3.13 (PA3); also elsewhere on the board
/SCL1: U3.45 (PB8); also elsewhere on the board
/SDA1: U3.46 (PB9); also elsewhere on the board
/STM32F103C8T6/CLK: J8.3, U3.37 (PA14)
/STM32F103C8T6/DAC_CS: U3.18 (PB0); also elsewhere on the board
/STM32F103C8T6/DAC_ERR_INT: U3.26 (PB13); also elsewhere on the board
/STM32F103C8T6/DIO: J8.2, U3.34 (PA13)
/UART3_RX: U3.22 (PB11); also elsewhere on the board
/UART3_TX: U3.21 (PB10); also elsewhere on the board
BUTTON: C26.1, R19.2, SW2.2, U3.30 (PA9)
LED2: R17.1, U3.39 (PB3)
unnamed: D6.2 (A), R17.2
unnamed: D7.2 (A), R18.2
unnamed: J7.2, R15.1, U3.44 (BOOT0)
unnamed: C17.1, R16.2, SW1.2, U3.7 (NRST)
unnamed: C15.1, U3.3 (PC14-OSC32_IN), Y1.1
unnamed: C18.1, U3.4 (PC15-OSC32_OUT), Y1.2
unnamed: C25.1, U3.5 (PD0_OSC_IN), Y2.3
unnamed: C24.1, U3.6 (PD1_OSC_OUT), Y2.1

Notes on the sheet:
CL=2*(CLoad-Cstray)

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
